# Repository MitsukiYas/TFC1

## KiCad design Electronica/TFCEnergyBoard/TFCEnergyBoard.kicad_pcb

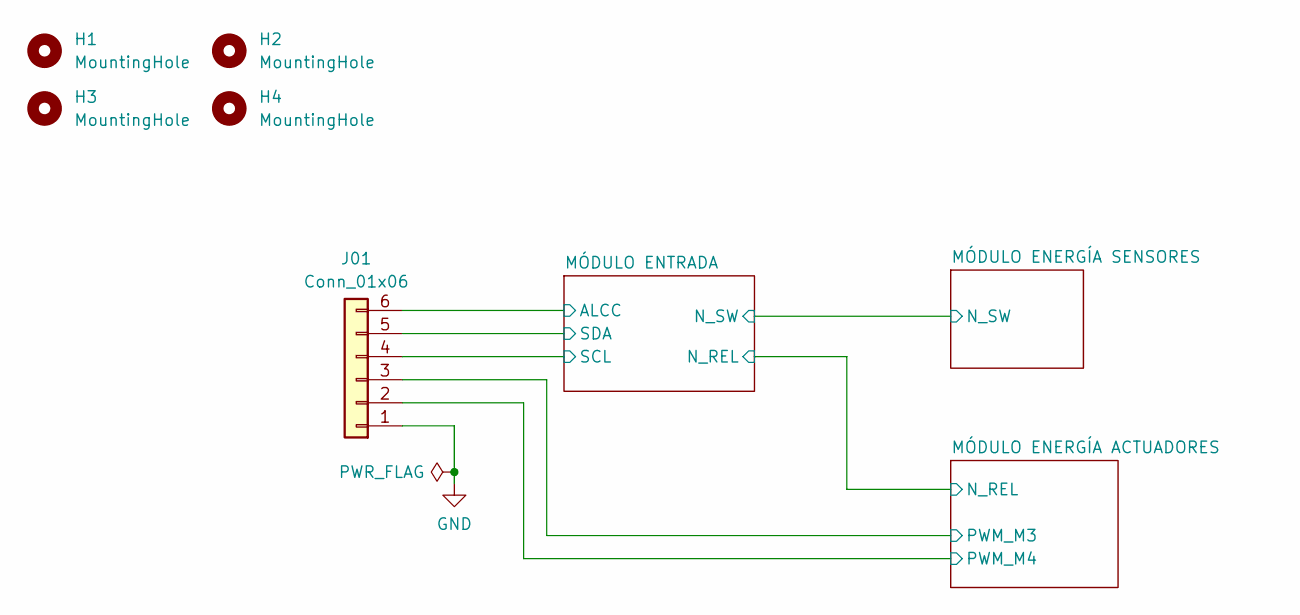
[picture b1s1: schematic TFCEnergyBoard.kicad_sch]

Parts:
H1, H2, H3, H4: MountingHole; MountingHole_3.2mm_M3
J01: Conn_01x06; JST_XH_B6B-XH-A_1x06_P2.50mm_Vertical

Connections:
/MÓDULO ENERGÍA ACTUADORES/PWM_M3: J01.3; also elsewhere on the board
/MÓDULO ENERGÍA ACTUADORES/PWM_M4: J01.2; also elsewhere on the board
/MÓDULO ENTRADA/ALCC: J01.6; also elsewhere on the board
/MÓDULO ENTRADA/SCL: J01.4; also elsewhere on the board
/MÓDULO ENTRADA/SDA: J01.5; also elsewhere on the board
GND: J01.1; also elsewhere on the board

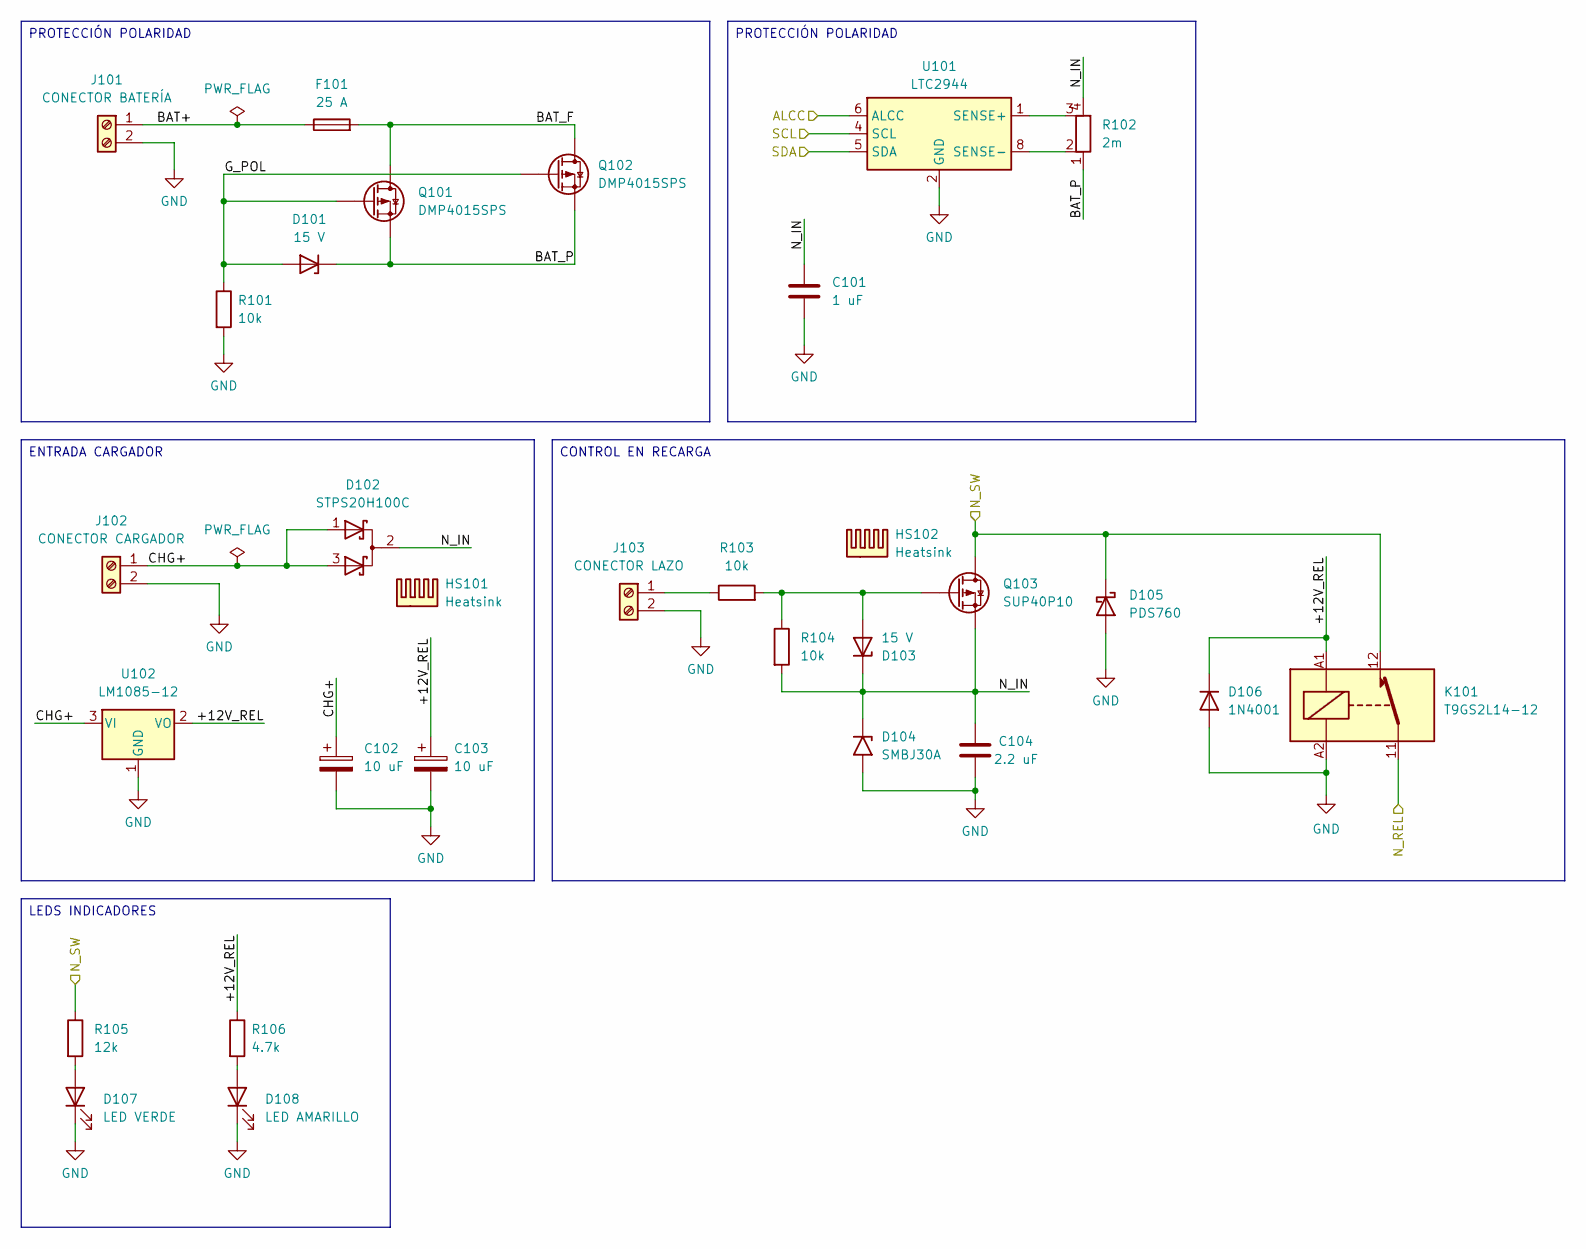
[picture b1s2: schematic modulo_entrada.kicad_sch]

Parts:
C101: 1 uF; C_0805_2012Metric
C102: 10 uF; CP_Elec_6.3x7.7
C103: 10 uF; CP_EIA-3528-21_Kemet-B
C104: 2.2 uF; C_1210_3225Metric
D101, D103: 15 V; D_SOD-123
D102: STPS20H100C; TO-220-3_Vertical
D104: SMBJ30A; D_SMB
D105: PDS760; D_PowerDI-5
D106: 1N4001; D_SMA
D107: LED VERDE; LED_0805_2012Metric
D108: LED AMARILLO; LED_0805_2012Metric
F101: 25 A; Fuse_Blade_ATO_directSolder
HS101, HS102: Heatsink; 529802B02500G
J101: CONECTOR BATERÍA; WE_691218410002
J102: CONECTOR CARGADOR; TerminalBlock_Phoenix_MKDS-3-2-5.08_1x02_P5.08mm_Horizontal
J103: CONECTOR LAZO; TerminalBlock_Phoenix_MKDS-1,5-2-5.08_1x02_P5.08mm_Horizont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
K101: T9GS2L14-12; T9GS2L1412
Q101, Q102: DMP4015SPS; PQFN-8-EP_6x5mm_P1.27mm_Generic
Q103: SUP40P10; TO-220-3_Vertical
R101, R103, R104: 10k; R_1206_3216Metric
R102: 2m; RES-SMD_4P_WSL36376L000FEA
R105: 12k; R_0805_2012Metric
R106: 4.7k; R_0805_2012Metric
U101: LTC2944; DFN-8-1EP_3x3mm_P0.5mm_EP1.65x2.38mm
U102: LM1085-12; TO-263-3_TabPin2

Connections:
/MÓDULO ENERGÍA ACTUADORES/N_REL: K101.11; also elsewhere on the board
/MÓDULO ENERGÍA SENSORES/N_SW: D105.1 (K), K101.12, Q103.2 (D), R105.1; also elsewhere on the board
/MÓDULO ENTRADA/+12V_REL: C103.1, D106.1 (K), K101.A1, R106.1, U102.2 (VO)
/MÓDULO ENTRADA/ALCC: U101.6 (ALCC); also elsewhere on the board
/MÓDULO ENTRADA/BAT+: F101.1, J101.1
/MÓDULO ENTRADA/BAT_F: F101.2, Q101.5 (D), Q102.5 (D)
/MÓDULO ENTRADA/BAT_P: D101.1 (K), Q101.1 (S), Q101.2 (S), Q101.3 (S), Q102.1 (S), Q102.2 (S), Q102.3 (S), R102.1
/MÓDULO ENTRADA/CHG+: C102.1, D102.1 (A), D102.3 (A), J102.1, U102.3 (VI)
/MÓDULO ENTRADA/G_POL: D101.2 (A), Q101.4 (G), Q102.4 (G), R101.1
/MÓDULO ENTRADA/N_IN: C101.1, C104.1, D102.2 (K), D103.1 (K), D104.1 (A1), Q103.3 (S), R102.4, R104.2
/MÓDULO ENTRADA/SCL: U101.4 (SCL); also elsewhere on the board
/MÓDULO ENTRADA/SDA: U101.5 (SDA); also elsewhere on the board
GND: C101.2, C102.2, C103.2, C104.2, D104.2 (A2), D105.2 (A), D106.2 (A), D107.1 (K), D108.1 (K), J101.2, J102.2, J103.2, K101.A2, R101.2, U101.2 (GND), U101.3 (GND), U101.7 (GND), U101.9 (GND), U102.1 (GND); also elsewhere on the board
unnamed: D103.2 (A), Q103.1 (G), R103.2, R104.1
unnamed: D107.2 (A), R105.2
unnamed: D108.2 (A), R106.2
unnamed: J103.1, R103.1
unnamed: R102.3, U101.1 (SENSE+)
unnamed: R102.2, U101.8 (SENSE-)

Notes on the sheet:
PROTECCIÓN POLARIDAD
ENTRADA CARGADOR
LEDS INDICADORES
CONTROL EN RECARGA

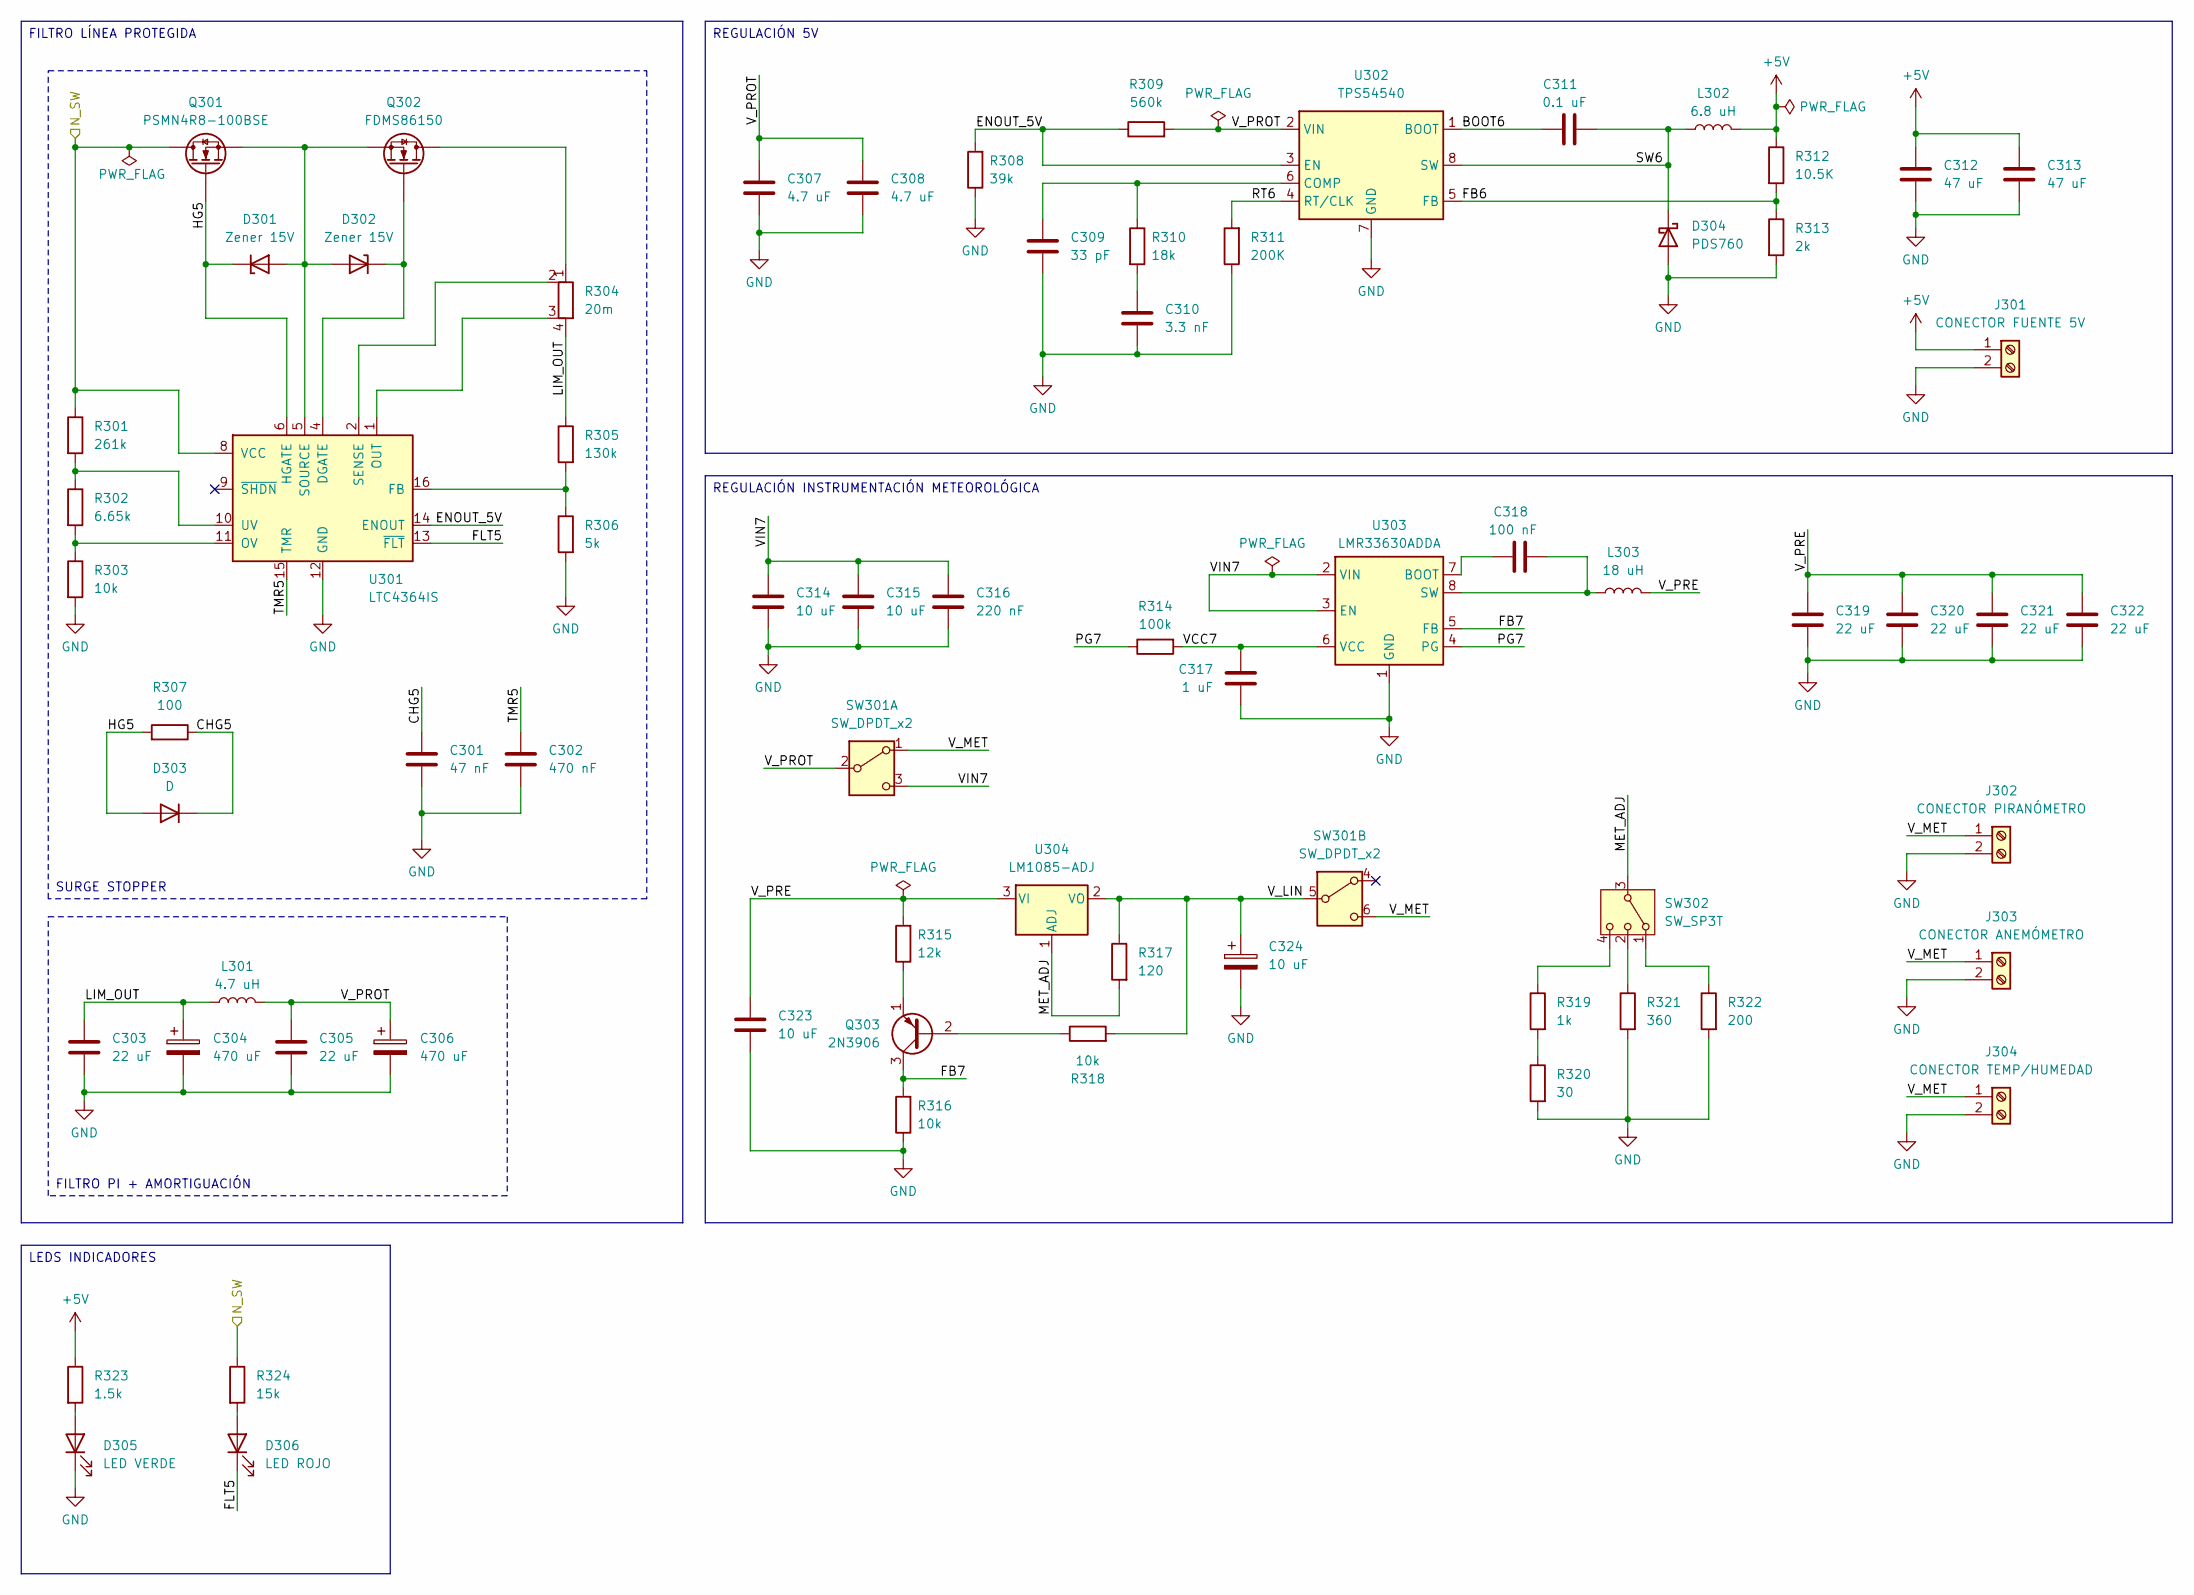
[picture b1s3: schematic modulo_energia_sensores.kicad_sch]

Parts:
C301: 47 nF; C_0805_2012Metric
C302: 470 nF; C_1206_3216Metric
C303, C305, C319, C320, C321, C322: 22 uF; C_1210_3225Metric
C304, C306: 470 uF; CP_Radial_D10.0mm_P5.00mm
C307, C308: 4.7 uF; C_1210_3225Metric
C309: 33 pF; C_0805_2012Metric
C310: 3.3 nF; C_0805_2012Metric
C311: 0.1 uF; C_0805_2012Metric
C312, C313: 47 uF; C_1210_3225Metric
C314, C315: 10 uF; C_1210_3225Metric
C316: 220 nF; C_0805_2012Metric
C317: 1 uF; C_0805_2012Metric
C318: 100 nF; C_0805_2012Metric
C323: 10 uF; C_1206_3216Metric
C324: 10 uF; CP_EIA-3528-21_Kemet-B
D301, D302: Zener 15V; D_SOD-123
D303: D; D_SOD-123
D304: PDS760; D_PowerDI-5
D305: LED VERDE; LED_0805_2012Metric
D306: LED ROJO; LED_0805_2012Metric
J301: CONECTOR FUENTE 5V; TerminalBlock_Phoenix_MKDS-3-2-5.08_1x02_P5.08mm_Horizontal
J302: CONECTOR PIRANÓMETRO; TerminalBlock_Phoenix_MKDS-1,5-2-5.08_1x02_P5.08mm_Horizont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
J303: CONECTOR ANEMÓMETRO; TerminalBlock_Phoenix_MKDS-1,5-2-5.08_1x02_P5.08mm_Horizont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
J304: CONECTOR TEMP/HUMEDAD; TerminalBlock_Phoenix_MKDS-1,5-2-5.08_1x02_P5.08mm_Horizont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
L301: 4.7 uH; L_Toroid_Horizontal_D17.3mm_P15.24mm_Bourns_2000
L302: 6.8 uH; L_Vishay_IHLP-5050
L303: 18 uH; L_Bourns_SRP1245A
Q301: PSMN4R8-100BSE; TO-263-3_TabPin2
Q302: FDMS86150; PQFN-8-EP_6x5mm_P1.27mm_Generic
Q303: 2N3906; TO-92_Inline
R301: 261k; R_0805_2012Metric
R302: 6.65k; R_0805_2012Metric
R303, R316, R318: 10k; R_0805_2012Metric
R304: 20m; R_Shunt_Vishay_WSK2512_6332Metric_T1.19mm
R305: 130k; R_0805_2012Metric
R306: 5k; R_0805_2012Metric
R307: 100; R_0805_2012Metric
R308: 39k; R_0805_2012Metric
R309: 560k; R_0805_2012Metric
R310: 18k; R_0805_2012Metric
R311: 200K; R_0805_2012Metric
R312: 10.5K; R_0805_2012Metric
R313: 2k; R_0805_2012Metric
R314: 100k; R_0805_2012Metric
R315: 12k; R_0805_2012Metric
R317: 120; R_0805_2012Metric
R319: 1k; R_0805_2012Metric
R320: 30; R_0805_2012Metric
R321: 360; R_0805_2012Metric
R322: 200; R_0805_2012Metric
R323: 1.5k; R_0805_2012Metric
R324: 15k; R_0805_2012Metric
SW301: SW_DPDT_x2; SolderWire-0.5sqmm_1x06_P4.6mm_D0.9mm_OD2.1mm
SW302: SW_SP3T; SolderWire-0.25sqmm_1x04_P4.2mm_D0.65mm_OD1.7mm
U301: LTC4364IS; SOIC-16_3.9x9.9mm_P1.27mm
U302: TPS54540; Texas_R-PDSO-G8_EP2.95x4.9mm_Mask2.4x3.1mm_ThermalVias
U303: LMR33630ADDA; Texas_HSOP-8-1EP_3.9x4.9mm_P1.27mm_ThermalVias
U304: LM1085-ADJ; TO-263-3_TabPin2

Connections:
+5V: C312.1, C313.1, J301.1, L302.2, R312.1, R323.1
/MÓDULO ENERGÍA SENSORES/BOOT6: C311.2, U302.1 (BOOT)
/MÓDULO ENERGÍA SENSORES/CHG5: C301.1, D303.1 (K), R307.1
/MÓDULO ENERGÍA SENSORES/ENOUT_5V: R308.2, R309.1, U301.14 (ENOUT), U302.3 (EN)
/MÓDULO ENERGÍA SENSORES/FB6: R312.2, R313.1, U302.5 (FB)
/MÓDULO ENERGÍA SENSORES/FB7: Q303.3 (C), R316.2, U303.5 (FB)
/MÓDULO ENERGÍA SENSORES/FLT5: D306.1 (K), U301.13 (~FLT)
/MÓDULO ENERGÍA SENSORES/HG5: D301.1 (K), D303.2 (A), Q301.1 (G), R307.2, U301.6 (HGATE)
/MÓDULO ENERGÍA SENSORES/LIM_OUT: C303.1, C304.1, L301.1, R304.4, R305.1
/MÓDULO ENERGÍA SENSORES/MET_ADJ: R317.2, SW302.3, U304.1 (ADJ)
/MÓDULO ENERGÍA SENSORES/N_SW: Q301.2 (D), R301.1, R324.1, U301.8 (VCC); also elsewhere on the board
/MÓDULO ENERGÍA SENSORES/PG7: R314.1, U303.4 (PG)
/MÓDULO ENERGÍA SENSORES/RT6: R311.2, U302.4 (RT/CLK)
/MÓDULO ENERGÍA SENSORES/SW6: C311.1, D304.1 (K), L302.1, U302.8 (SW)
/MÓDULO ENERGÍA SENSORES/TMR5: C302.1, U301.15 (TMR)
/MÓDULO ENERGÍA SENSORES/VCC7: C317.1, R314.2, U303.6 (VCC)
/MÓDULO ENERGÍA SENSORES/VIN7: C314.1, C315.1, C316.1, SW301.3 (C), U303.2 (VIN), U303.3 (EN)
/MÓDULO ENERGÍA SENSORES/V_LIN: C324.1, R317.1, R318.2, SW301.5 (B), U304.2 (VO)
/MÓDULO ENERGÍA SENSORES/V_MET: J302.1, J303.1, J304.1, SW301.1 (A), SW301.6 (C)
/MÓDULO ENERGÍA SENSORES/V_PRE: C319.1, C320.1, C321.1, C322.1, C323.1, L303.2, R315.2, U304.3 (VI)
/MÓDULO ENERGÍA SENSORES/V_PROT: C305.1, C306.1, C307.1, C308.1, L301.2, R309.2, SW301.2 (B), U302.2 (VIN)
GND: C301.2, C302.2, C303.2, C304.2, C305.2, C306.2, C307.2, C308.2, C309.2, C310.2, C312.2, C313.2, C314.2, C315.2, C316.2, C317.2, C319.2, C320.2, C321.2, C322.2, C323.2, C324.2, D304.2 (A), D305.1 (K), J301.2, J302.2, J303.2, J304.2, R303.2, R306.2, R308.1, R311.1, R313.2, R316.1, R320.2, R321.2, R322.2, U301.12 (GND), U302.7 (GND), U302.9 (GND), U303.1 (GND), U303.9 (GND); also elsewhere on the board
unnamed: C310.1, R310.2
unnamed: D301.2 (A), D302.2 (A), Q301.3 (S), Q302.1 (S), Q302.2 (S), Q302.3 (S), U301.5 (SOURCE)
unnamed: D302.1 (K), Q302.4 (G), U301.4 (DGATE)
unnamed: D305.2 (A), R323.2
unnamed: D306.2 (A), R324.2
unnamed: Q302.5 (D), R304.1
unnamed: Q303.2 (B), R318.1
unnamed: Q303.1 (E), R315.1
unnamed: R319.1, SW302.4
unnamed: R319.2, R320.1
unnamed: R321.1, SW302.2
unnamed: R322.1, SW302.1
unnamed: R305.2, R306.1, U301.16 (FB)
unnamed: R304.3, U301.1 (OUT)
unnamed: R302.2, R303.1, U301.11 (OV)
unnamed: R304.2, U301.2 (SENSE)
unnamed: R301.2, R302.1, U301.10 (UV)
unnamed: C309.1, R310.1, U302.6 (COMP)
unnamed: C318.2, U303.7 (BOOT)
unnamed: C318.1, L303.1, U303.8 (SW)

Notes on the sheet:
FILTRO LÍNEA PROTEGIDA
FILTRO PI + AMORTIGUACIÓN
LEDS INDICADORES
REGULACIÓN 5V
REGULACIÓN INSTRUMENTACIÓN METEOROLÓGICA
SURGE STOPPER

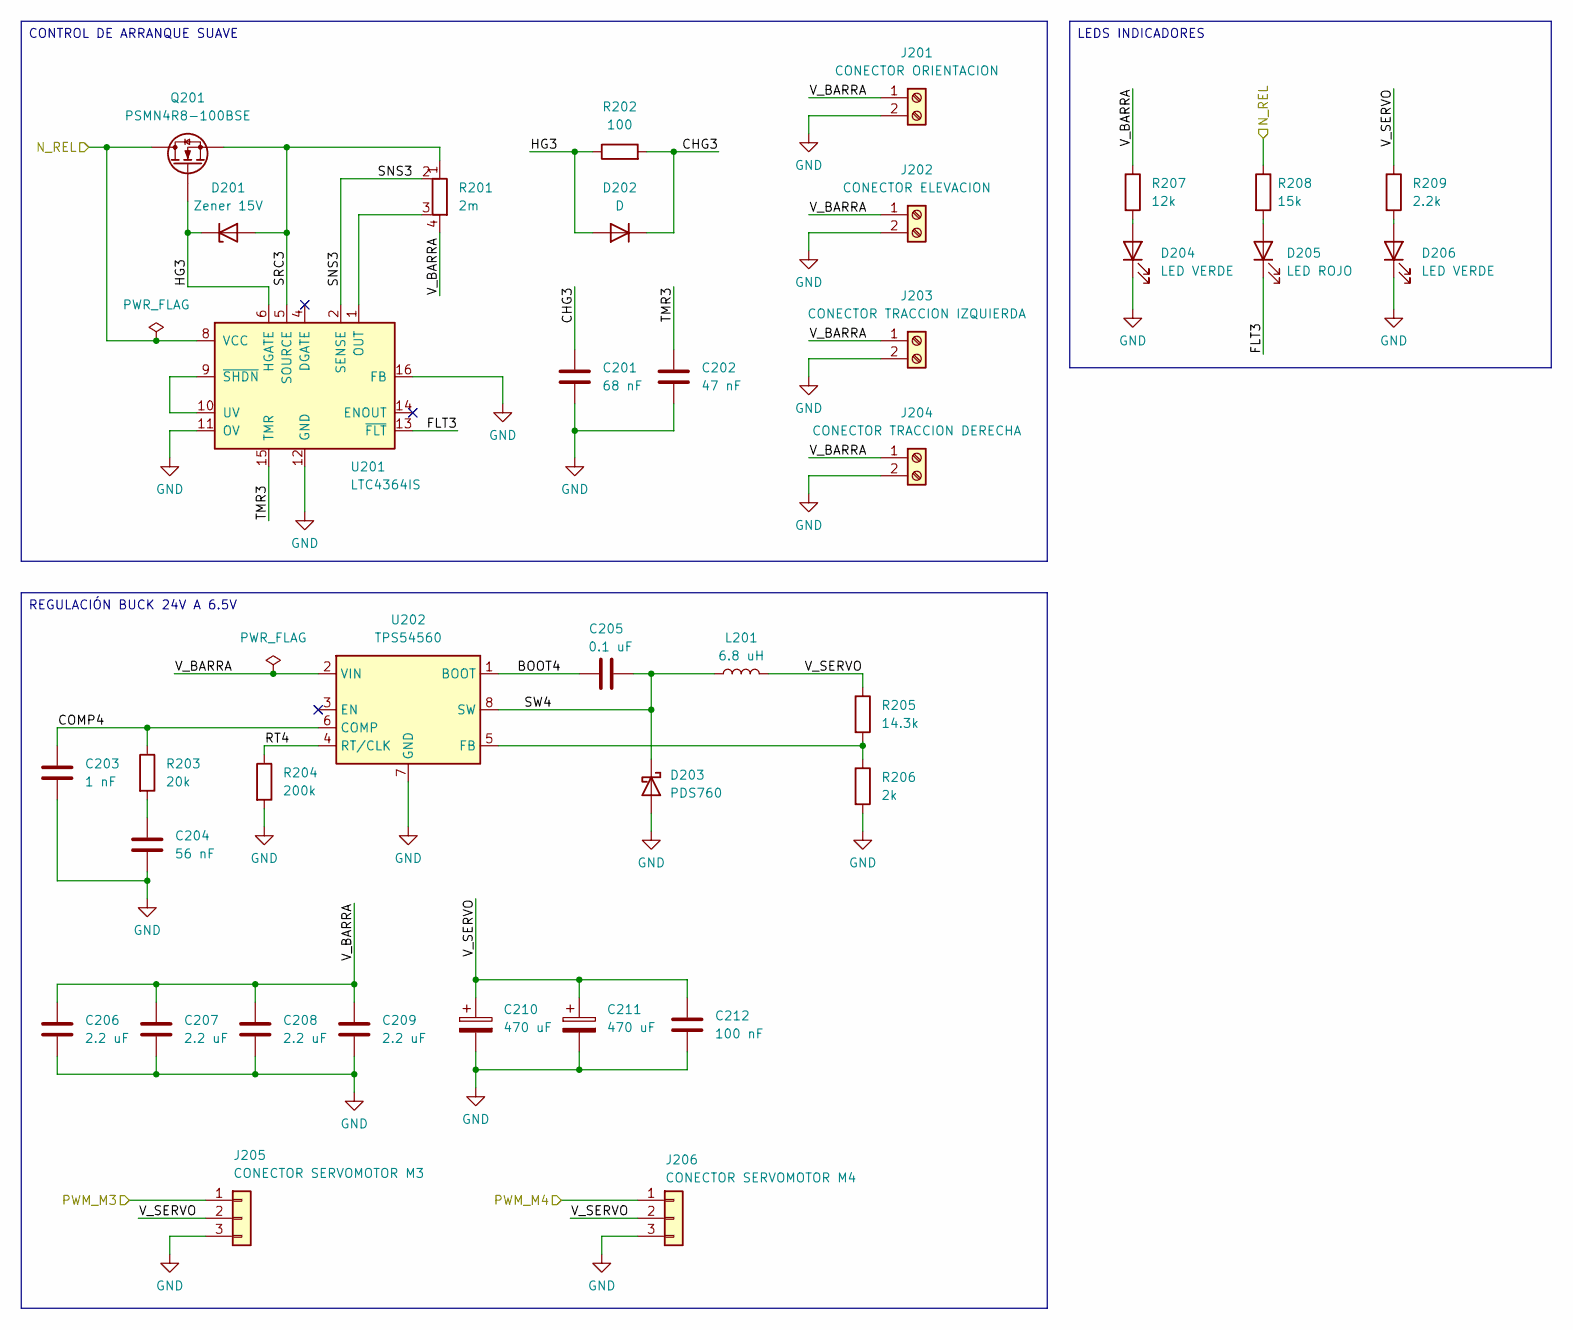
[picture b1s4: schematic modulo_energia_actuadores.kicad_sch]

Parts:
C201: 68 nF; C_0805_2012Metric
C202: 47 nF; C_0805_2012Metric
C203: 1 nF; C_0805_2012Metric
C204: 56 nF; C_0805_2012Metric
C205: 0.1 uF; C_0805_2012Metric
C206, C207, C208, C209: 2.2 uF; C_1210_3225Metric
C210, C211: 470 uF; CP_Radial_D10.0mm_P5.00mm
C212: 100 nF; C_0805_2012Metric
D201: Zener 15V; D_SOD-123
D202: D; D_SOD-123
D203: PDS760; D_PowerDI-5
D204, D206: LED VERDE; LED_0805_2012Metric
D205: LED ROJO; LED_0805_2012Metric
J201: CONECTOR ORIENTACION; TerminalBlock_Phoenix_MKDS-3-2-5.08_1x02_P5.08mm_Horizontal
J202: CONECTOR ELEVACION; TerminalBlock_Phoenix_MKDS-3-2-5.08_1x02_P5.08mm_Horizontal
J203: CONECTOR TRACCION IZQUIERDA; TerminalBlock_Phoenix_MKDS-3-2-5.08_1x02_P5.08mm_Horizontal
J204: CONECTOR TRACCION DERECHA; TerminalBlock_Phoenix_MKDS-3-2-5.08_1x02_P5.08mm_Horizontal
J205: CONECTOR SERVOMOTOR M3; PinHeader_1x03_P2.54mm_Vertical
J206: CONECTOR SERVOMOTOR M4; PinHeader_1x03_P2.54mm_Vertical
L201: 6.8 uH; L_Vishay_IHLP-5050
Q201: PSMN4R8-100BSE; TO-263-3_TabPin2
R201: 2m; R_Shunt_Vishay_WSK2512_6332Metric_T1.19mm
R202: 100; R_0805_2012Metric
R203: 20k; R_0805_2012Metric
R204: 200k; R_0805_2012Metric
R205: 14.3k; R_0805_2012Metric
R206: 2k; R_0805_2012Metric
R207: 12k; R_0805_2012Metric
R208: 15k; R_0805_2012Metric
R209: 2.2k; R_0805_2012Metric
U201: LTC4364IS; SOIC-16_3.9x9.9mm_P1.27mm
U202: TPS54560; Texas_R-PDSO-G8_EP2.95x4.9mm_Mask2.4x3.1mm_ThermalVias

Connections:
/MÓDULO ENERGÍA ACTUADORES/BOOT4: C205.2, U202.1 (BOOT)
/MÓDULO ENERGÍA ACTUADORES/CHG3: C201.1, D202.1 (K), R202.2
/MÓDULO ENERGÍA ACTUADORES/COMP4: C203.1, R203.1, U202.6 (COMP)
/MÓDULO ENERGÍA ACTUADORES/FLT3: D205.1 (K), U201.13 (~FLT)
/MÓDULO ENERGÍA ACTUADORES/HG3: D201.1 (K), D202.2 (A), Q201.1 (G), R202.1, U201.6 (HGATE)
/MÓDULO ENERGÍA ACTUADORES/N_REL: Q201.2 (D), R208.1, U201.8 (VCC); also elsewhere on the board
/MÓDULO ENERGÍA ACTUADORES/PWM_M3: J205.1; also elsewhere on the board
/MÓDULO ENERGÍA ACTUADORES/PWM_M4: J206.1; also elsewhere on the board
/MÓDULO ENERGÍA ACTUADORES/RT4: R204.1, U202.4 (RT/CLK)
/MÓDULO ENERGÍA ACTUADORES/SNS3: R201.2, U201.2 (SENSE)
/MÓDULO ENERGÍA ACTUADORES/SRC3: D201.2 (A), Q201.3 (S), R201.1, U201.5 (SOURCE)
/MÓDULO ENERGÍA ACTUADORES/SW4: C205.1, D203.1 (K), L201.1, U202.8 (SW)
/MÓDULO ENERGÍA ACTUADORES/TMR3: C202.1, U201.15 (TMR)
/MÓDULO ENERGÍA ACTUADORES/V_BARRA: C206.1, C207.1, C208.1, C209.1, J201.1, J202.1, J203.1, J204.1, R201.4, R207.1, U202.2 (VIN)
/MÓDULO ENERGÍA ACTUADORES/V_SERVO: C210.1, C211.1, C212.1, J205.2, J206.2, L201.2, R205.1, R209.1
GND: C201.2, C202.2, C203.2, C204.2, C206.2, C207.2, C208.2, C209.2, C210.2, C211.2, C212.2, D203.2 (A), D204.1 (K), D206.1 (K), J201.2, J202.2, J203.2, J204.2, J205.3, J206.3, R204.2, R206.2, U201.11 (OV), U201.12 (GND), U201.16 (FB), U202.7 (GND), U202.9 (GND); also elsewhere on the board
unnamed: C204.1, R203.2
unnamed: D204.2 (A), R207.2
unnamed: D205.2 (A), R208.2
unnamed: D206.2 (A), R209.2
unnamed: R201.3, U201.1 (OUT)
unnamed: U201.9 (~SHDN), U201.10 (UV)
unnamed: R205.2, R206.1, U202.5 (FB)

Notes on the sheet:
REGULACIÓN BUCK 24V A 6.5V
CONTROL DE ARRANQUE SUAVE
LEDS INDICADORES

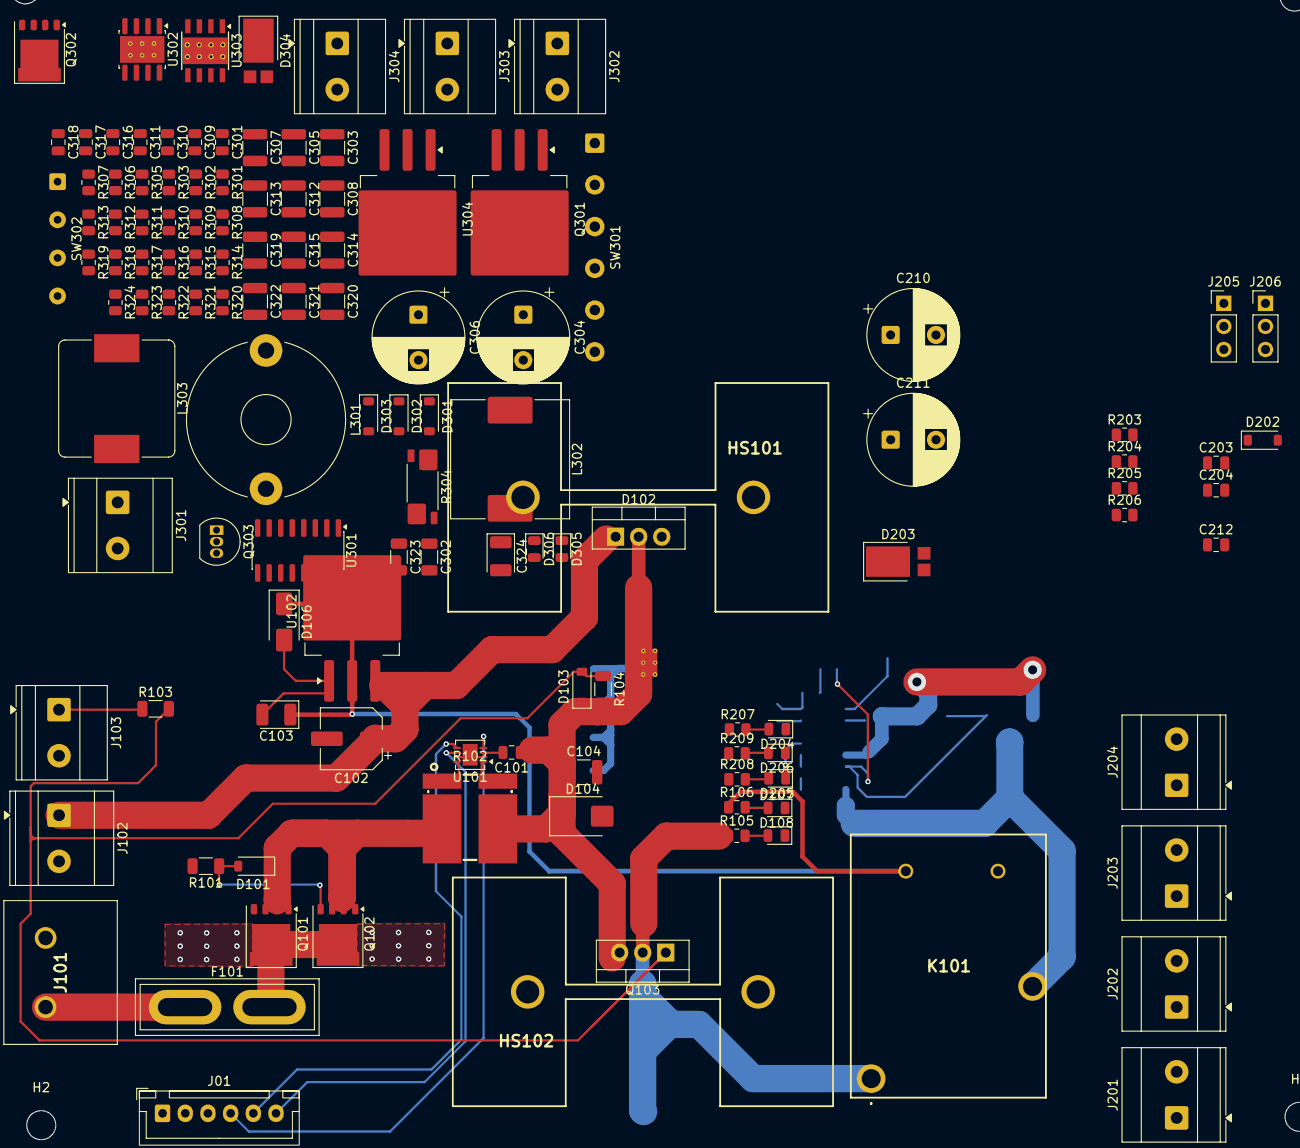
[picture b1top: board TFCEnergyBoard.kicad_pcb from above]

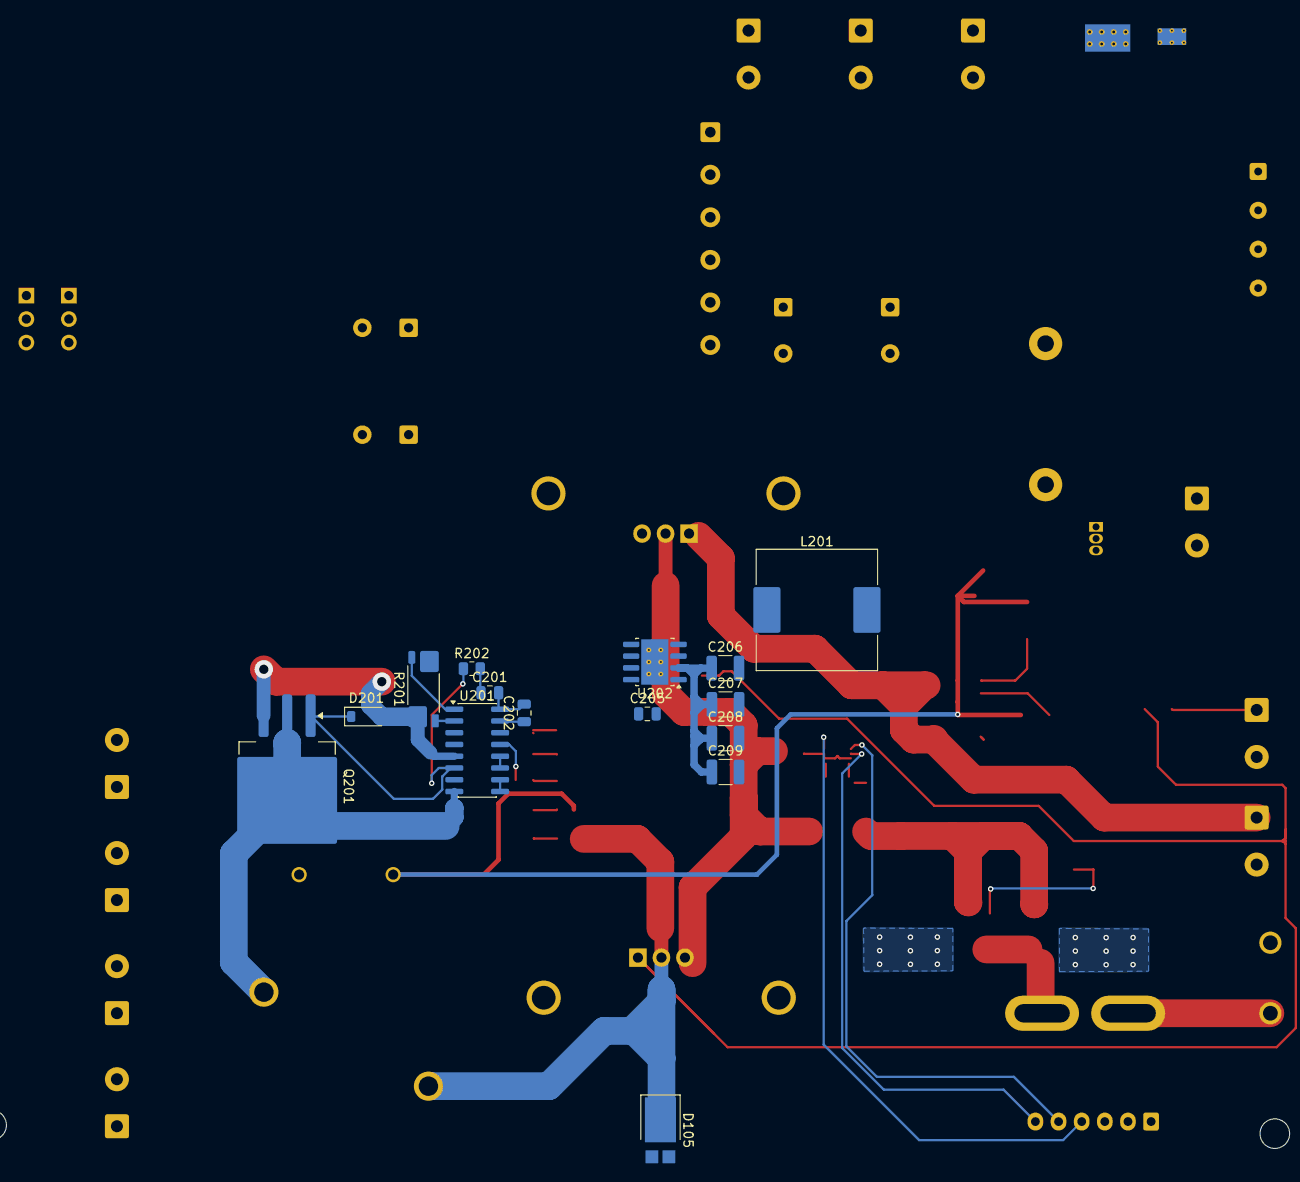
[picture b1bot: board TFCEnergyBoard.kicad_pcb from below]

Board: 4 copper layers, 142 parts (15 on the bottom side), 80 nets.
